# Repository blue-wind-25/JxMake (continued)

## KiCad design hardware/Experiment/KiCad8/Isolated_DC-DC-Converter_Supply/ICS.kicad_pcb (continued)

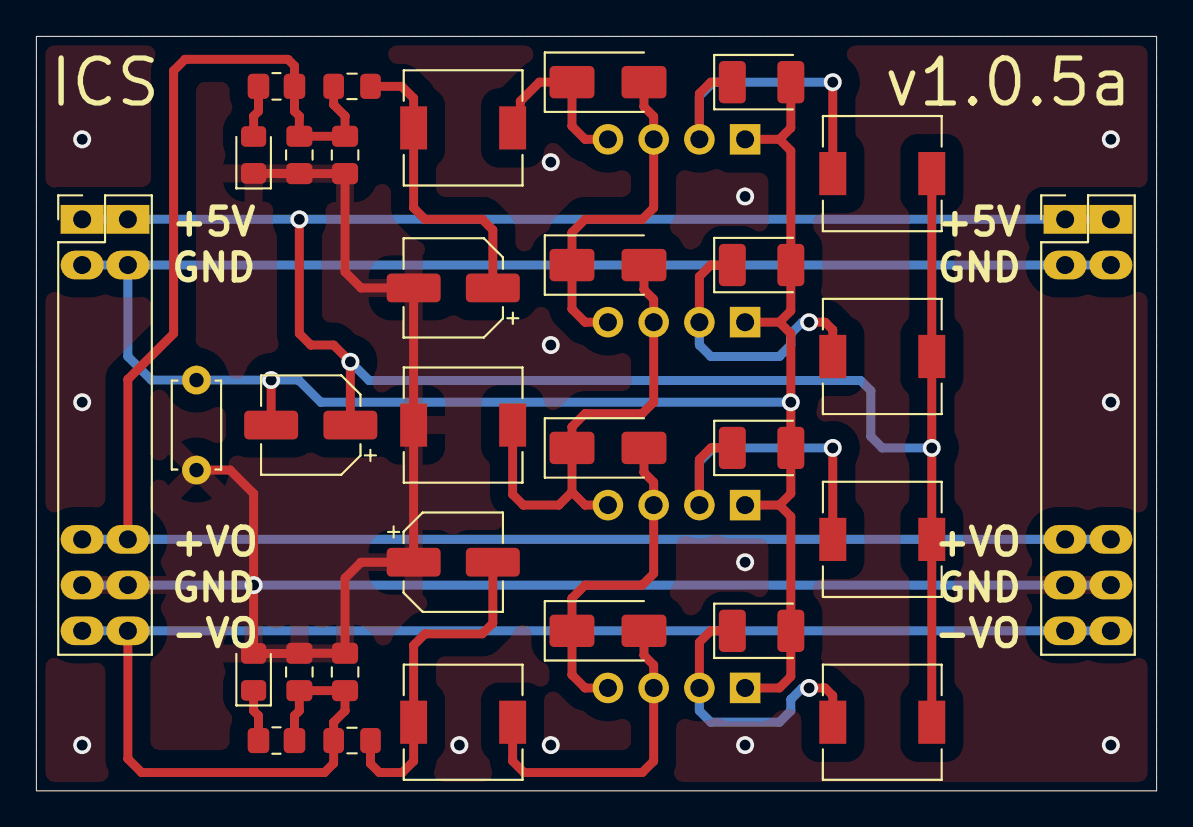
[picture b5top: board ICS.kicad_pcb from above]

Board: 2 copper layers, 62.2 x 41.9 mm, 35 parts (0 on the bottom side), 18 nets.

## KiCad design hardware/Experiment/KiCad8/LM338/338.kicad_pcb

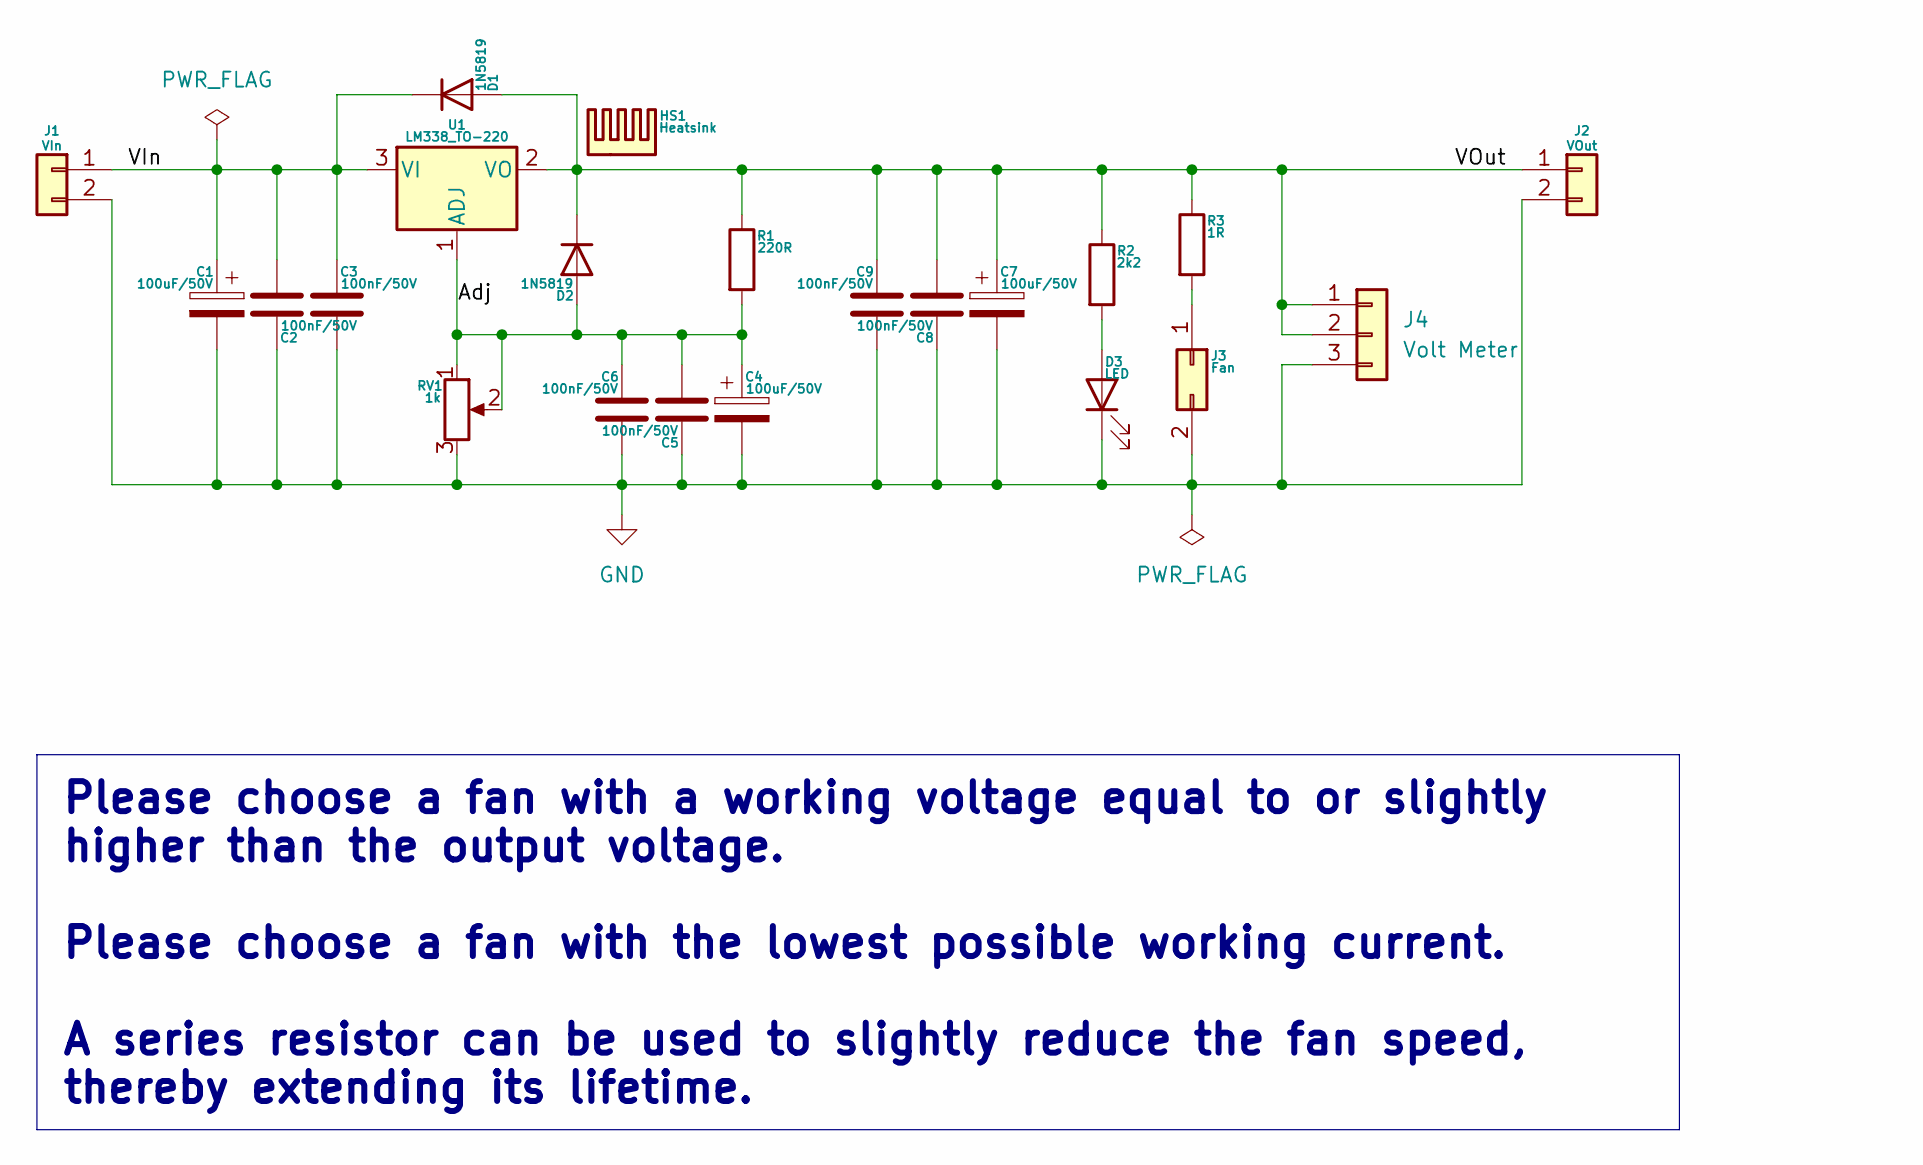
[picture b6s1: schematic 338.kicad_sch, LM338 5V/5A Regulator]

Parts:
C1, C4, C7: 100uF/50V; CP_Radial_D10.0mm_P2.50mm
C2, C3, C5, C6, C8, C9: 100nF/50V; C_Disc_D3.0mm_W1.6mm_P2.50mm
D1, D2: 1N5819; D_A-405_P7.62mm_Horizontal
D3: LED; LED_D3.0mm_Clear
HS1: Heatsink; Heatsink_Stonecold_HS-S01_13.21x6.35mm
J1: VIn; PinHeader_1x02_P2.54mm_Vertical
J2: VOut; PinHeader_1x02_P2.54mm_Vertical
J3: Fan; PinHeader_1x02_P2.54mm_Vertical
J4: Volt Meter; FanPinHeader_1x03_P2.54mm_Vertical
R1: 220R; R_Axial_DIN0207_L6.3mm_D2.5mm_P7.62mm_Horizontal
R2: 2k2; R_Axial_DIN0207_L6.3mm_D2.5mm_P7.62mm_Horizontal
R3: 1R; R_Axial_DIN0207_L6.3mm_D2.5mm_P7.62mm_Horizontal
RV1: 1k; Potentiometer_Bourns_3296W_Vertical
U1: LM338_TO-220; TO-220-3_Vertical

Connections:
/Adj: C4.1, C5.2, C6.1, D2.2 (A), R1.2, RV1.1, RV1.2, U1.1 (ADJ)
/VIn: C1.1, C2.2, C3.1, D1.1 (K), J1.1, U1.3 (VI)
/VOut: C7.1, C8.2, C9.1, D1.2 (A), D2.1 (K), J2.1, J4.1, J4.2, R1.1, R2.1, R3.1, U1.2 (VO)
GND: C1.2, C2.1, C3.2, C4.2, C5.1, C6.2, C7.2, C8.1, C9.2, D3.1 (K), J1.2, J2.2, J3.2, J4.3, RV1.3
unnamed: D3.2 (A), R2.2
unnamed: J3.1, R3.2

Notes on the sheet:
Please choose a fan with a working voltage equal to or slightly higher than the output voltage. Please choose a fan with the lowest possible working current. A series resistor can be used to slightly reduce the fan speed, thereby extending its lifetime.

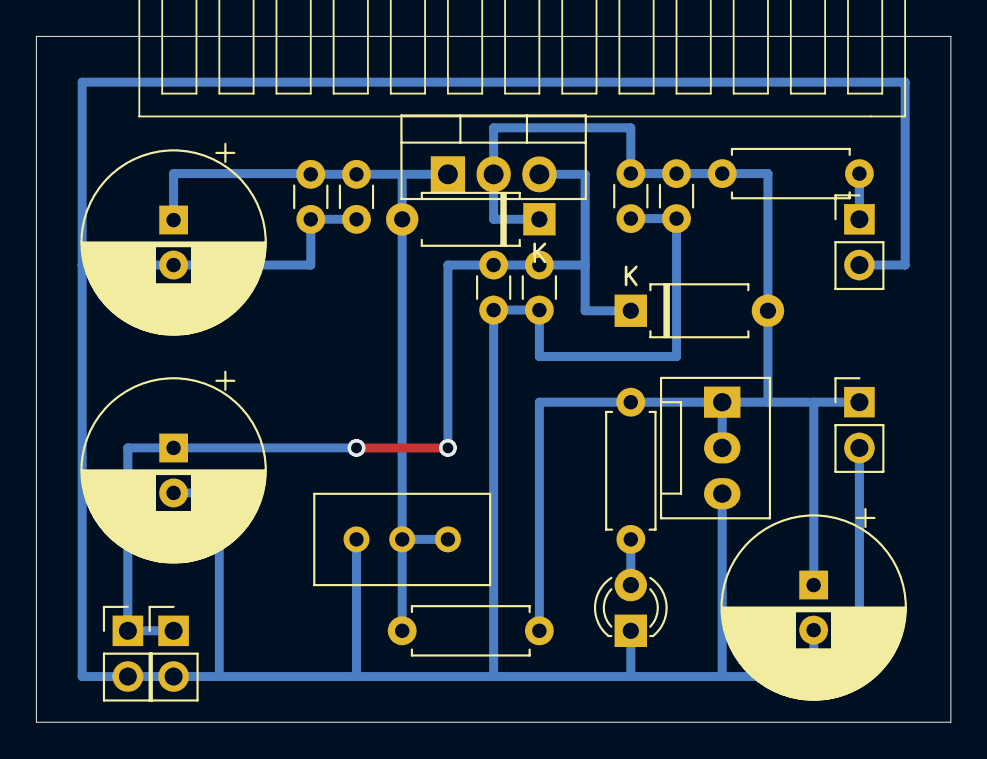
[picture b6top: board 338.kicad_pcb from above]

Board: 2 copper layers, 50.8 x 38.1 mm, 22 parts (0 on the bottom side), 6 nets.

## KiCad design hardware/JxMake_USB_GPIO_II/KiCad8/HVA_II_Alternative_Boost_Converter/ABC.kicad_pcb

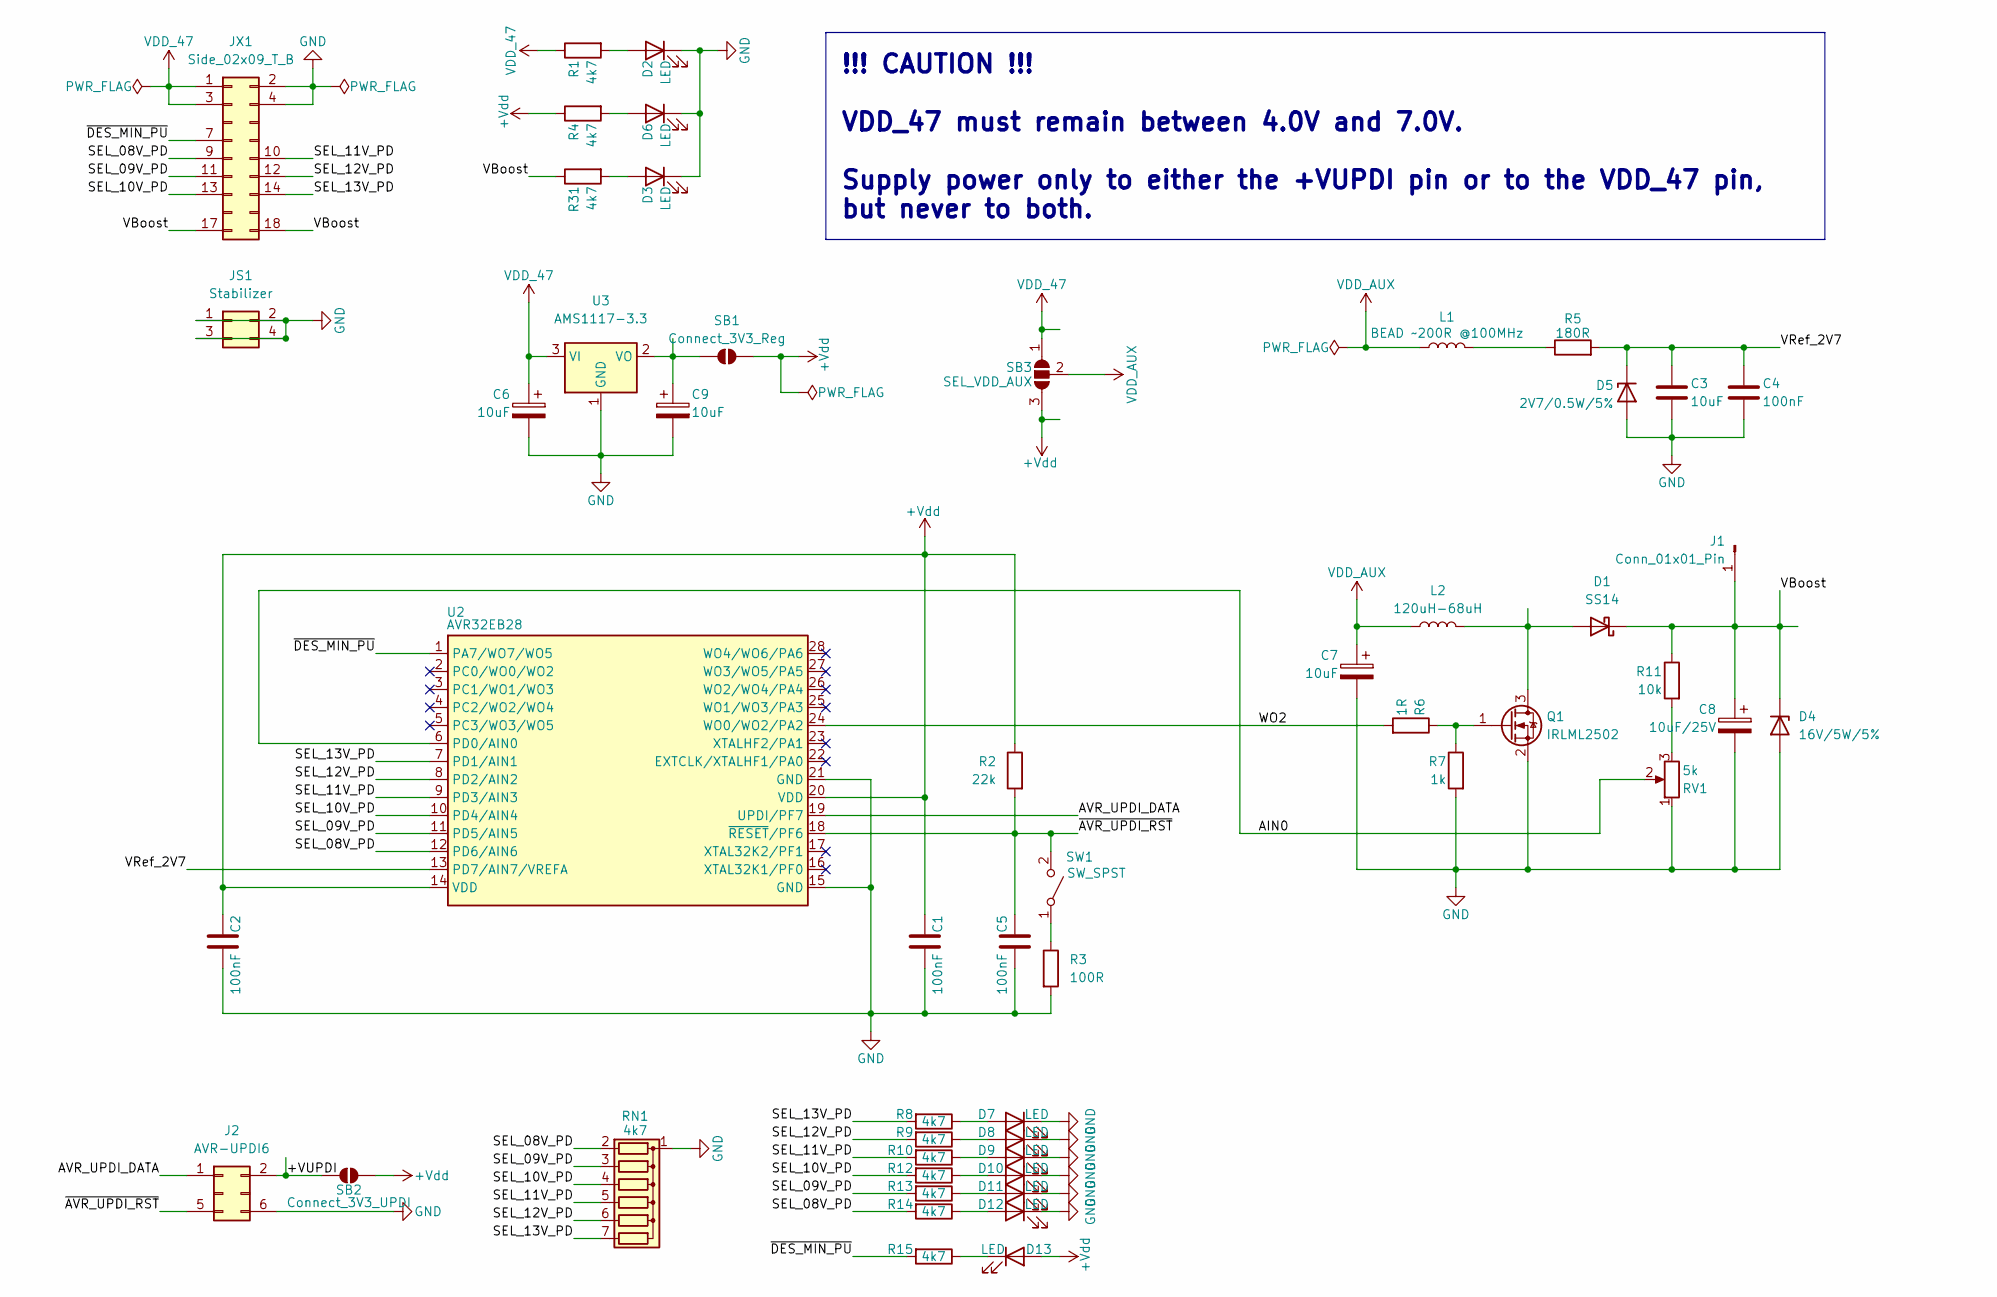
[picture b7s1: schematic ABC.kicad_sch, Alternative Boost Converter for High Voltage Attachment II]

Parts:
C1, C2, C4, C5: 100nF; C_0805_2012Metric_Pad1.18x1.45mm_HandSolder
C3: 10uF; C_1206_3216Metric_Pad1.33x1.80mm_HandSolder
C6, C7, C9: 10uF; CP_EIA-3528-21_Kemet-B_Pad1.50x2.35mm_HandSolder
C8: 10uF/25V; CP_EIA-3528-21_Kemet-B_Pad1.50x2.35mm_HandSolder
D1: SS14; D_SMA
D2, D3, D6, D7, D8, D9, D10, D11, D12, D13: LED; LED_0805_2012Metric_Pad1.15x1.40mm_HandSolder
D4: 16V/5W/5%; D_5W_P10.16mm_Horizontal
D5: 2V7/0.5W/5%; D_MELF_Handsoldering
J1: Conn_01x01_Pin; PinHeader_1x01_P2.00mm_Vertical
J2: AVR-UPDI6; IDC-Header_2x03_P2.54mm_Vertical
JS1: Stabilizer; PinHeader_2x02_P2.54mm_Vertical
JX1: Side_02x09_T_B; PinHeader_2x09_P2.54mm_Vertical
L1: BEAD ~200R @100MHz; L_0805_2012Metric_Pad1.15x1.40mm_HandSolder
L2: 120uH-68uH; L_Radial_D10.0mm_P5.00mm_Fastron_07M
Q1: IRLML2502; SOT-23_Handsoldering
R1, R4, R8, R9, R10, R12, R13, R14, R15, R31: 4k7; R_0805_2012Metric_Pad1.20x1.40mm_HandSolder
R2: 22k; R_0805_2012Metric_Pad1.20x1.40mm_HandSolder
R3: 100R; R_0805_2012Metric_Pad1.20x1.40mm_HandSolder
R5: 180R; R_0805_2012Metric_Pad1.20x1.40mm_HandSolder
R6: 1R; R_0805_2012Metric_Pad1.20x1.40mm_HandSolder
R7: 1k; R_0805_2012Metric_Pad1.20x1.40mm_HandSolder
R11: 10k; R_0805_2012Metric_Pad1.20x1.40mm_HandSolder
RN1: 4k7; R_Array_SIP7
RV1: 5k; Potentiometer_Bourns_3296W_Vertical
SB1: Connect_3V3_Reg; SolderJumper-2_P1.3mm_Open_RoundedPad1.0x1.5mm
SB2: Connect_3V3_UPDI; SolderJumper-2_P1.3mm_Open_RoundedPad1.0x1.5mm
SB3: SEL_VDD_AUX; SolderJumper-3_P1.3mm_Open_RoundedPad1.0x1.5mm
SW1: SW_SPST; SW_SPST_FSMSM
U2: AVR32EB28; SSOP-28_5.3x10.2mm_P0.65mm
U3: AMS1117-3.3; SOT-223-3_TabPin2

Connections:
+Vdd: C1.1, C2.1, D13.2 (A), R2.1, R4.1, SB1.2 (B), SB2.1 (A), SB3.3 (B), U2.14 (VDD), U2.20 (VDD)
/+VUPDI: J2.2, SB2.2 (B)
/AIN0: RV1.2, U2.6 (PD0/AIN0)
/AVR_UPDI_DATA: J2.1, U2.19 (UPDI/PF7)
/SEL_08V_PD: JX1.9, R14.2, RN1.2 (R1), U2.12 (PD6/AIN6)
/SEL_09V_PD: JX1.11, R13.2, RN1.3 (R2), U2.11 (PD5/AIN5)
/SEL_10V_PD: JX1.13, R12.2, RN1.4 (R3), U2.10 (PD4/AIN4)
/SEL_11V_PD: JX1.10, R10.2, RN1.5 (R4), U2.9 (PD3/AIN3)
/SEL_12V_PD: JX1.12, R9.2, RN1.6 (R5), U2.8 (PD2/AIN2)
/SEL_13V_PD: JX1.14, R8.2, RN1.7 (R6), U2.7 (PD1/AIN1)
/VBoost: C8.1, D1.1 (K), D4.1 (K), J1.1, JX1.17, JX1.18, R11.1, R31.1
/VRef_2V7: C3.1, C4.1, D5.1 (K), R5.2, U2.13 (PD7/AIN7/VREFA)
/WO2: R6.2, U2.24 (WO0/WO2/PA2)
/~AVR_UPDI_RST: C5.1, J2.5, R2.2, SW1.2 (B), U2.18 (~RESET/PF6)
/~DES_MIN_PU: JX1.7, R15.2, U2.1 (PA7/WO7/WO5)
GND: C1.2, C2.2, C3.2, C4.2, C5.2, C6.2, C7.2, C8.2, C9.2, D2.1 (K), D3.1 (K), D4.2 (A), D5.2 (A), D6.1 (K), D7.1 (K), D8.1 (K), D9.1 (K), D10.1 (K), D11.1 (K), D12.1 (K), J2.6, JS1.1, JS1.2, JS1.3, JS1.4, JX1.2, JX1.4, Q1.2 (S), R3.2, R7.2, RN1.1 (common), RV1.1, U2.15 (GND), U2.21 (GND), U3.1 (GND)
unnamed: D1.2 (A), L2.2, Q1.3 (D)
unnamed: D2.2 (A), R1.2
unnamed: D3.2 (A), R31.2
unnamed: D6.2 (A), R4.2
unnamed: D7.2 (A), R8.1
unnamed: D8.2 (A), R9.1
unnamed: D9.2 (A), R10.1
unnamed: D10.2 (A), R12.1
unnamed: D11.2 (A), R13.1
unnamed: D12.2 (A), R14.1
unnamed: D13.1 (K), R15.1
unnamed: L1.1, R5.1
unnamed: Q1.1 (G), R6.1, R7.1
unnamed: R11.2, RV1.3
unnamed: C9.1, SB1.1 (A), U3.2 (VO)
unnamed: R3.1, SW1.1 (A)
VDD_47: C6.1, JX1.1, JX1.3, R1.1, SB3.1 (A), U3.3 (VI)
VDD_AUX: C7.1, L1.2, L2.1, SB3.2 (C)

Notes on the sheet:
!!! CAUTION !!! VDD_47 must remain between 4.0V and 7.0V. Supply power only to either the +VUPDI pin or to the VDD_47 pin, but never to both.

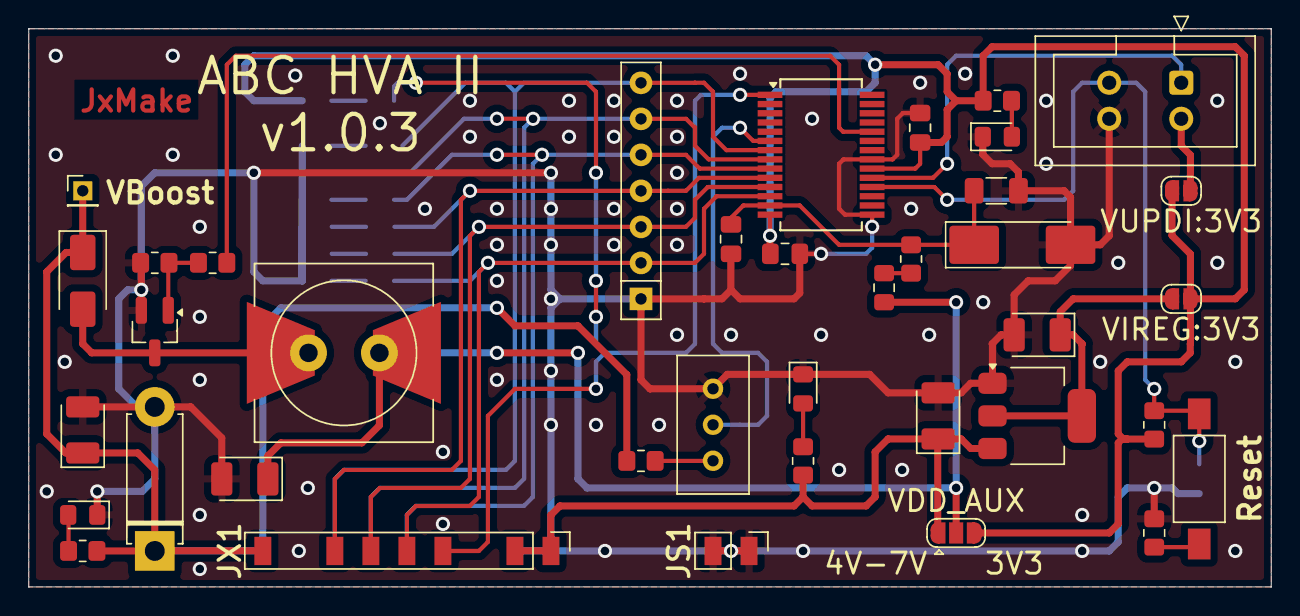
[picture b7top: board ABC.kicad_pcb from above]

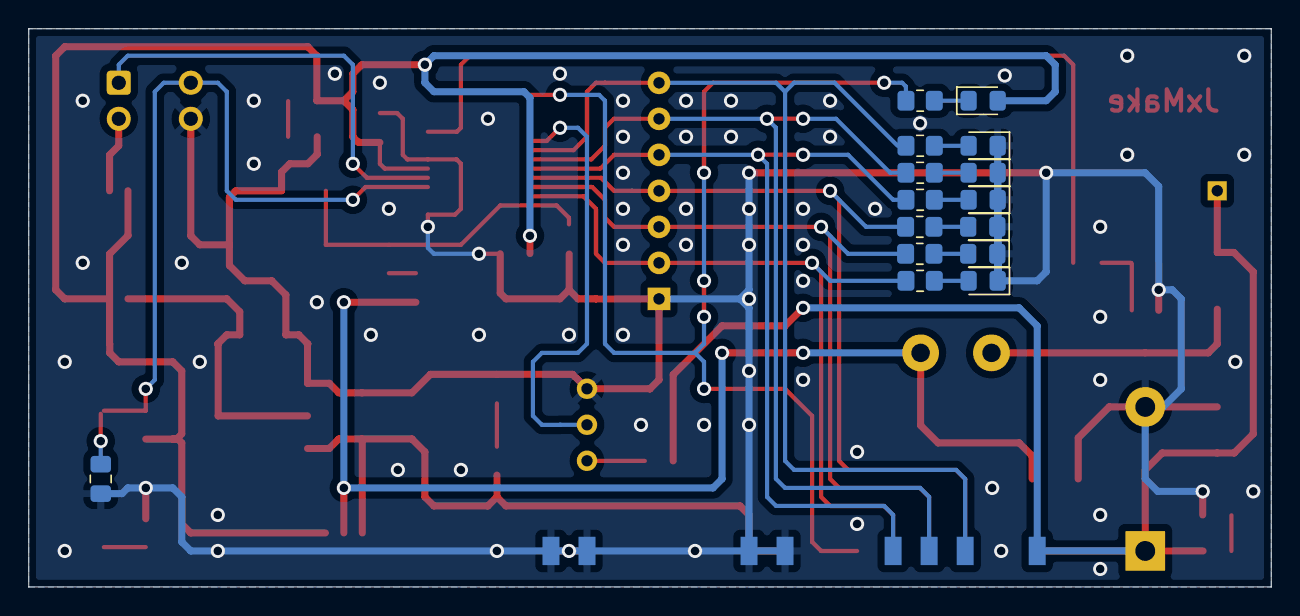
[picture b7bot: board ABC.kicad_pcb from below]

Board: 2 copper layers, 87.6 x 39.4 mm, 53 parts (15 on the bottom side), 34 nets.
